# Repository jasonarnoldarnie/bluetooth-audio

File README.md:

# bluetooth-audio
Hardware and firmware for bluetooth audio adaptor

## Repo setup

Hooks live in `.githooks/` (version controlled), so each clone needs one command to enable them:

```bash
git config core.hooksPath .githooks
```

The `pre-commit` hook re-stamps the "Updated" date in [`docs/design-overview.tex`](docs/design-overview.tex)
and renders [`docs/design-overview.pdf`](docs/design-overview.pdf) into the same commit. It runs only
when that document is staged, never blocks a commit, and needs [Tectonic](https://tectonic-typesetting.github.io/)
(XeTeX) on `PATH` or in `%LOCALAPPDATA%\Programs\Tectonic` (Python is used only for the date stamp).
The diagrams render in the Consolas monospace font (a Windows system font); on other platforms swap it
for another mono font with box-drawing glyphs in the document preamble.

- `git config hooks.designpdf false` — disable without deleting the hook
- `git config hooks.designpdf.snapshot true` — also keep a dated copy under `docs/snapshots/`

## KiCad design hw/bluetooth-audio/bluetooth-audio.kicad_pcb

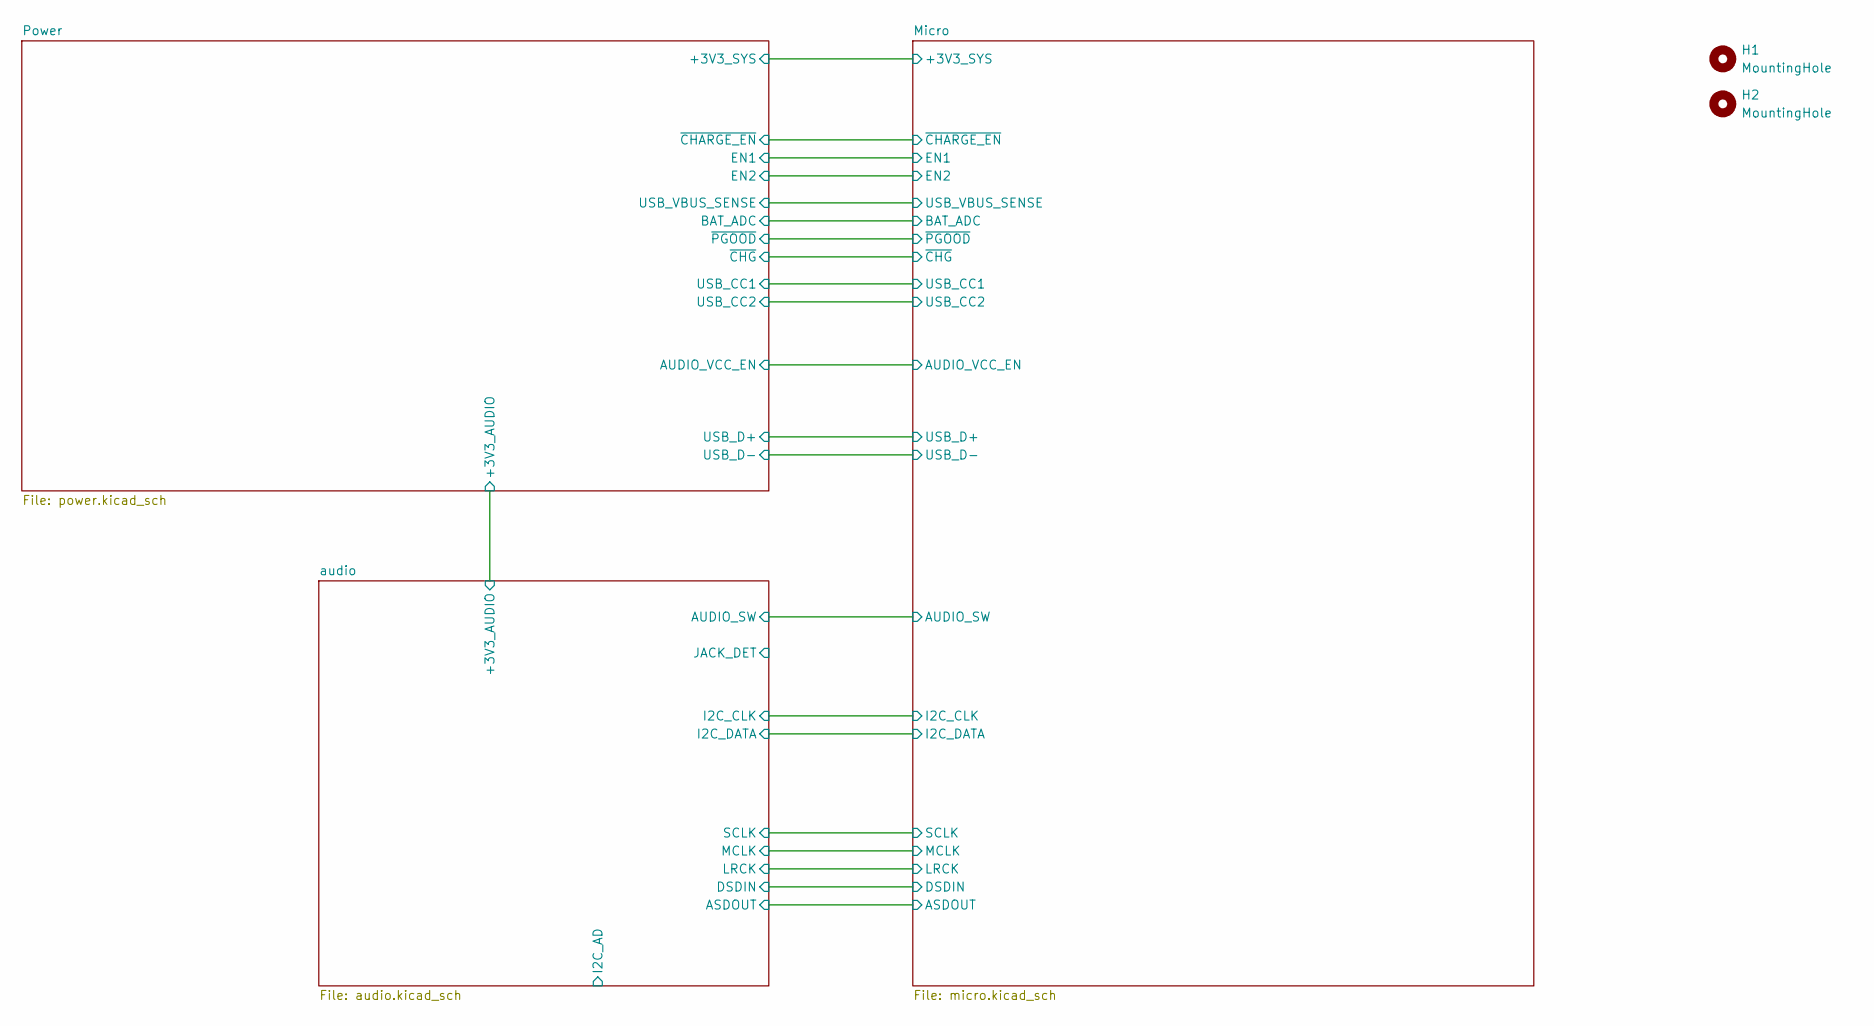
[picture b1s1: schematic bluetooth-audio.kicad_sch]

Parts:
H1, H2: MountingHole; MountingHole_2.2mm_M2_DIN965_Pad

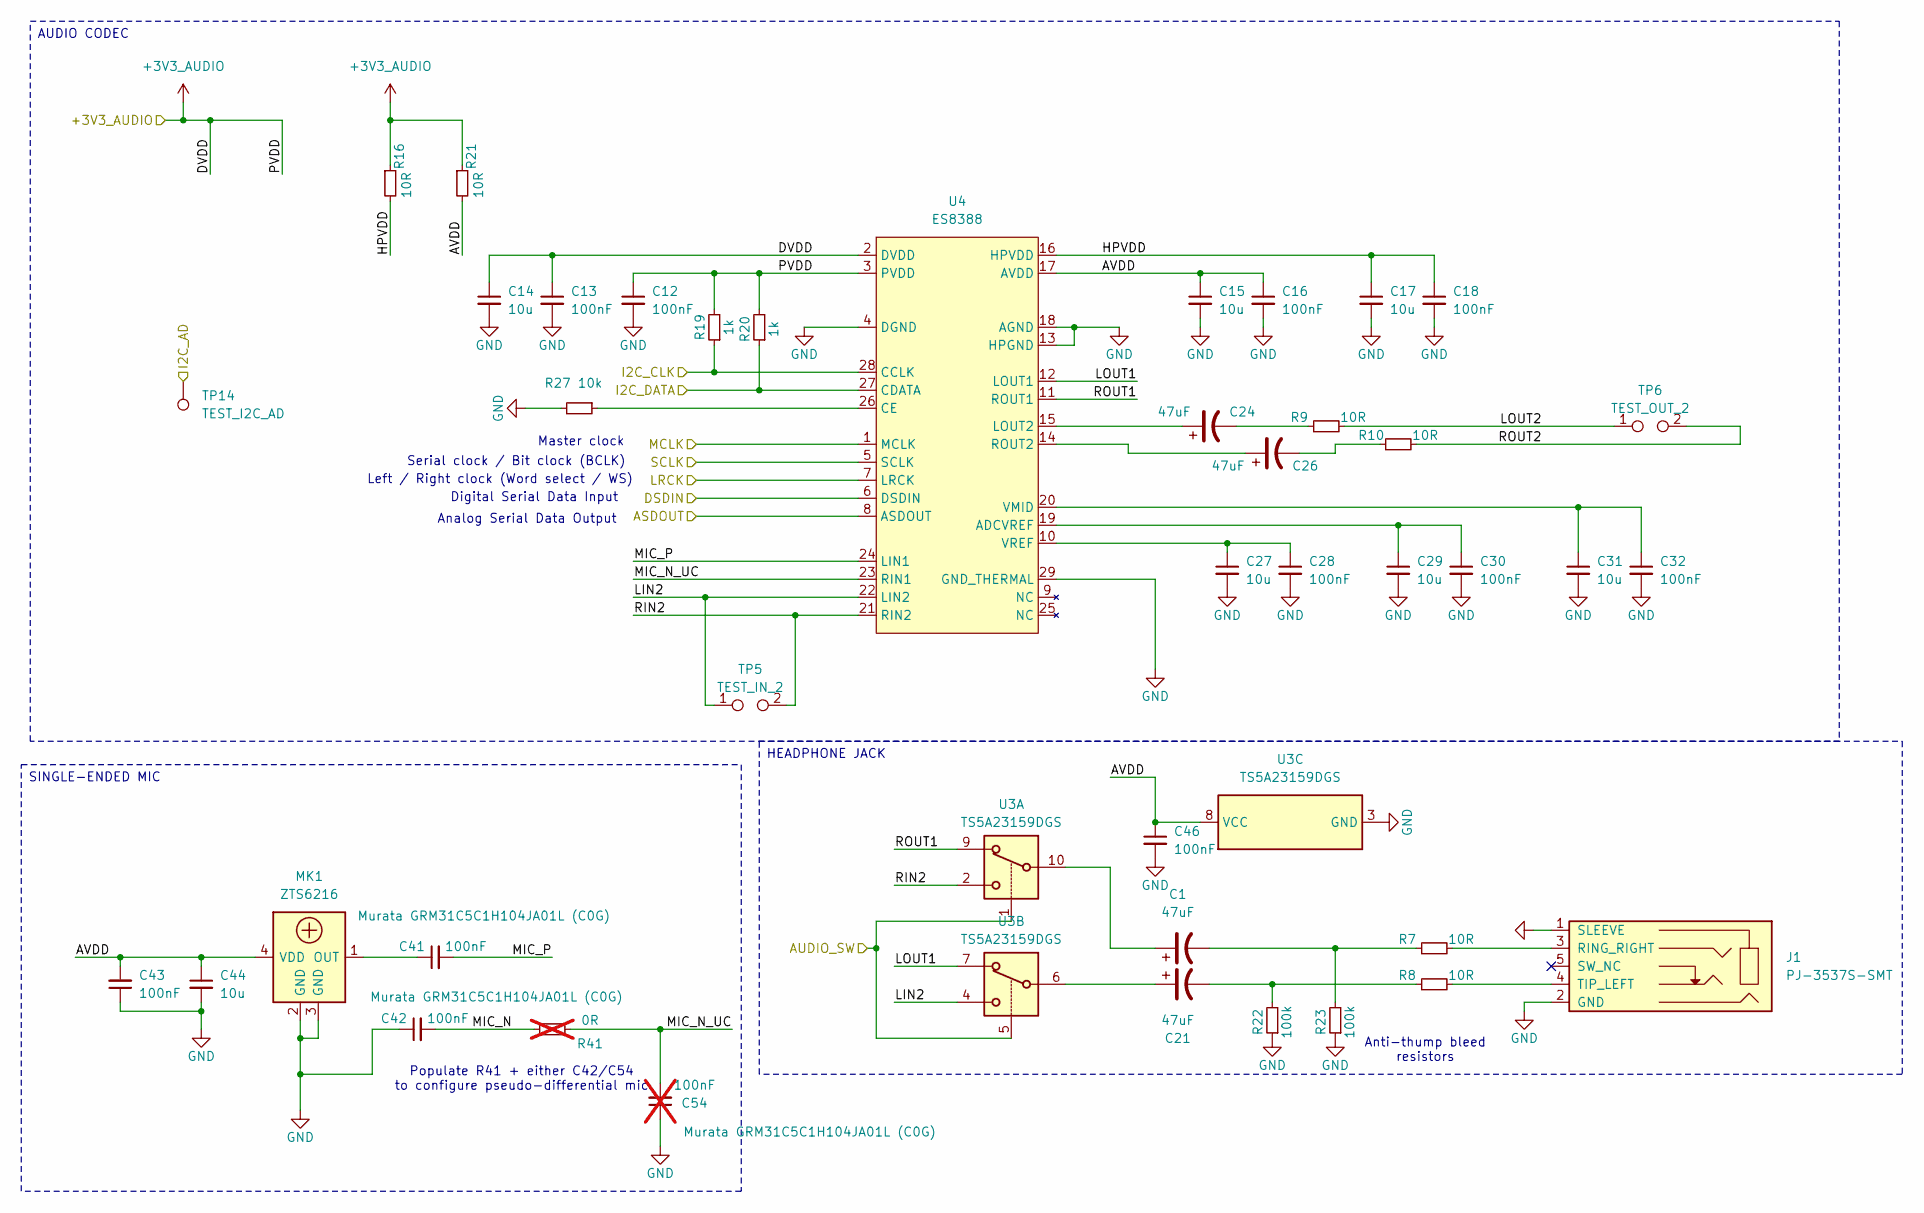
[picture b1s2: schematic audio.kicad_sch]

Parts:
C1, C21, C24, C26: 47uF; CP_Elec_5x5.8; MPN EEEFT1E470AR; LCSC C336270
C12, C13, C16, C18, C28, C30, C32, C43, C46: 100nF; C_0402_1005Metric; MPN CL05B104KO5NNNC; LCSC C1525
C14, C15, C17, C27, C29, C31, C44: 10u; C_0603_1608Metric; MPN CL10A106KP8NNNC; LCSC C19702
C41, C42: 100nF; C_1206_3216Metric; MPN GRM31C5C1H104JA01L; LCSC C97946
C54: 100nF; C_1206_3216Metric; MPN GRM31C5C1H104JA01L; LCSC C97946; not fitted
J1: PJ-3537S-SMT; MPN PJ-3537S-SMT; LCSC C2689709
MK1: ZTS6216; MPN ZTS6216; LCSC C481302
R7, R8, R9, R10, R16, R21: 10R; R_0402_1005Metric; MPN 0402WGF100JTCE; LCSC C25077
R19, R20: 1k; R_0402_1005Metric; MPN 0402WGF1001TCE; LCSC C11702
R22, R23: 100k; R_0402_1005Metric; MPN 0402WGF1003TCE; LCSC C25741
R27: 10k; R_0402_1005Metric; MPN 0402WGF1002TCE; LCSC C25744
R41: 0R; R_0402_1005Metric; MPN 0402WGF0000TCE; LCSC C17168; not fitted
TP5: TEST_IN_2; TestPoint_Pad_2x1_D1.0mm
TP6: TEST_OUT_2; TestPoint_Pad_2x1_D1.0mm
TP14: TEST_I2C_AD; TestPoint_Pad_D1.0mm
U3: TS5A23159DGS; MSOP-10_3x3mm_P0.5mm; MPN TS5A23159DGSR; LCSC C42751
U4: ES8388; QFN-28-1EP_4x4mm_P0.4mm_EP2.3x2.3mm; MPN ES8388; LCSC C365736

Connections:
+3V3_AUDIO: C12.1, C13.1, C14.1, R16.1, R19.2, R20.2, R21.1, U4.2 (DVDD), U4.3 (PVDD); also elsewhere on the board
/Micro/ASDOUT: U4.8 (ASDOUT); also elsewhere on the board
/Micro/AUDIO_SW: U3.1, U3.5; also elsewhere on the board
/Micro/DSDIN: U4.6 (DSDIN); also elsewhere on the board
/Micro/GPIO_0: U4.1 (MCLK); also elsewhere on the board
/Micro/I2C_CLK: R19.1, U4.28 (CCLK); also elsewhere on the board
/Micro/I2C_DATA: R20.1, U4.27 (CDATA); also elsewhere on the board
/Micro/LRCK: U4.7 (LRCK); also elsewhere on the board
/Micro/SCLK: U4.5 (SCLK); also elsewhere on the board
/audio/AVDD: C15.1, C16.1, C43.2, C44.1, C46.1, MK1.4 (VDD), R21.2, U3.8 (VCC), U4.17 (AVDD)
/audio/HPVDD: C17.1, C18.1, R16.2, U4.16 (HPVDD)
/audio/LIN2: TP5.1, U3.4, U4.22 (LIN2)
/audio/LOUT1: U3.7, U4.12 (LOUT1)
/audio/LOUT2: R9.2, TP6.1
/audio/MIC_N: C42.2, R41.1
/audio/MIC_N_UC: C54.2, R41.2, U4.23 (RIN1)
/audio/MIC_P: C41.2, U4.24 (LIN1)
/audio/RIN2: TP5.2, U3.2, U4.21 (RIN2)
/audio/ROUT1: U3.9, U4.11 (ROUT1)
/audio/ROUT2: R10.2, TP6.2
GND: C12.2, C13.2, C14.2, C15.2, C16.2, C17.2, C18.2, C27.2, C28.2, C29.2, C30.2, C31.2, C32.2, C42.1, C43.1, C44.2, C46.2, C54.1, J1.1 (SLEEVE), J1.2 (GND), MK1.2 (GND), MK1.3 (GND), R22.1, R23.1, R27.2, U3.3 (GND), U4.4 (DGND), U4.13 (HPGND), U4.18 (AGND), U4.29 (GND_THERMAL); also elsewhere on the board
unnamed: C1.1, U3.10
unnamed: C1.2, R7.1, R23.2
unnamed: C21.1, U3.6
unnamed: C21.2, R8.1, R22.2
unnamed: C24.2, R9.1
unnamed: C26.2, R10.1
unnamed: J1.3 (RING_RIGHT), R7.2
unnamed: J1.4 (TIP_LEFT), R8.2
unnamed: C41.1, MK1.1 (OUT)
unnamed: C29.1, C30.1, U4.19 (ADCVREF)
unnamed: R27.1, U4.26 (CE)
unnamed: C24.1, U4.15 (LOUT2)
unnamed: C26.1, U4.14 (ROUT2)
unnamed: C31.1, C32.1, U4.20 (VMID)
unnamed: C27.1, C28.1, U4.10 (VREF)

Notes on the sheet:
Anti-thump bleed resistors
Digital Serial Data Input
Left / Right clock (Word select / WS)
Populate R41 + either C42/C54 to configure pseudo-differential mic
Analog Serial Data Output
Master clock
Serial clock / Bit clock (BCLK)
SINGLE-ENDED MIC
HEADPHONE JACK
AUDIO CODEC

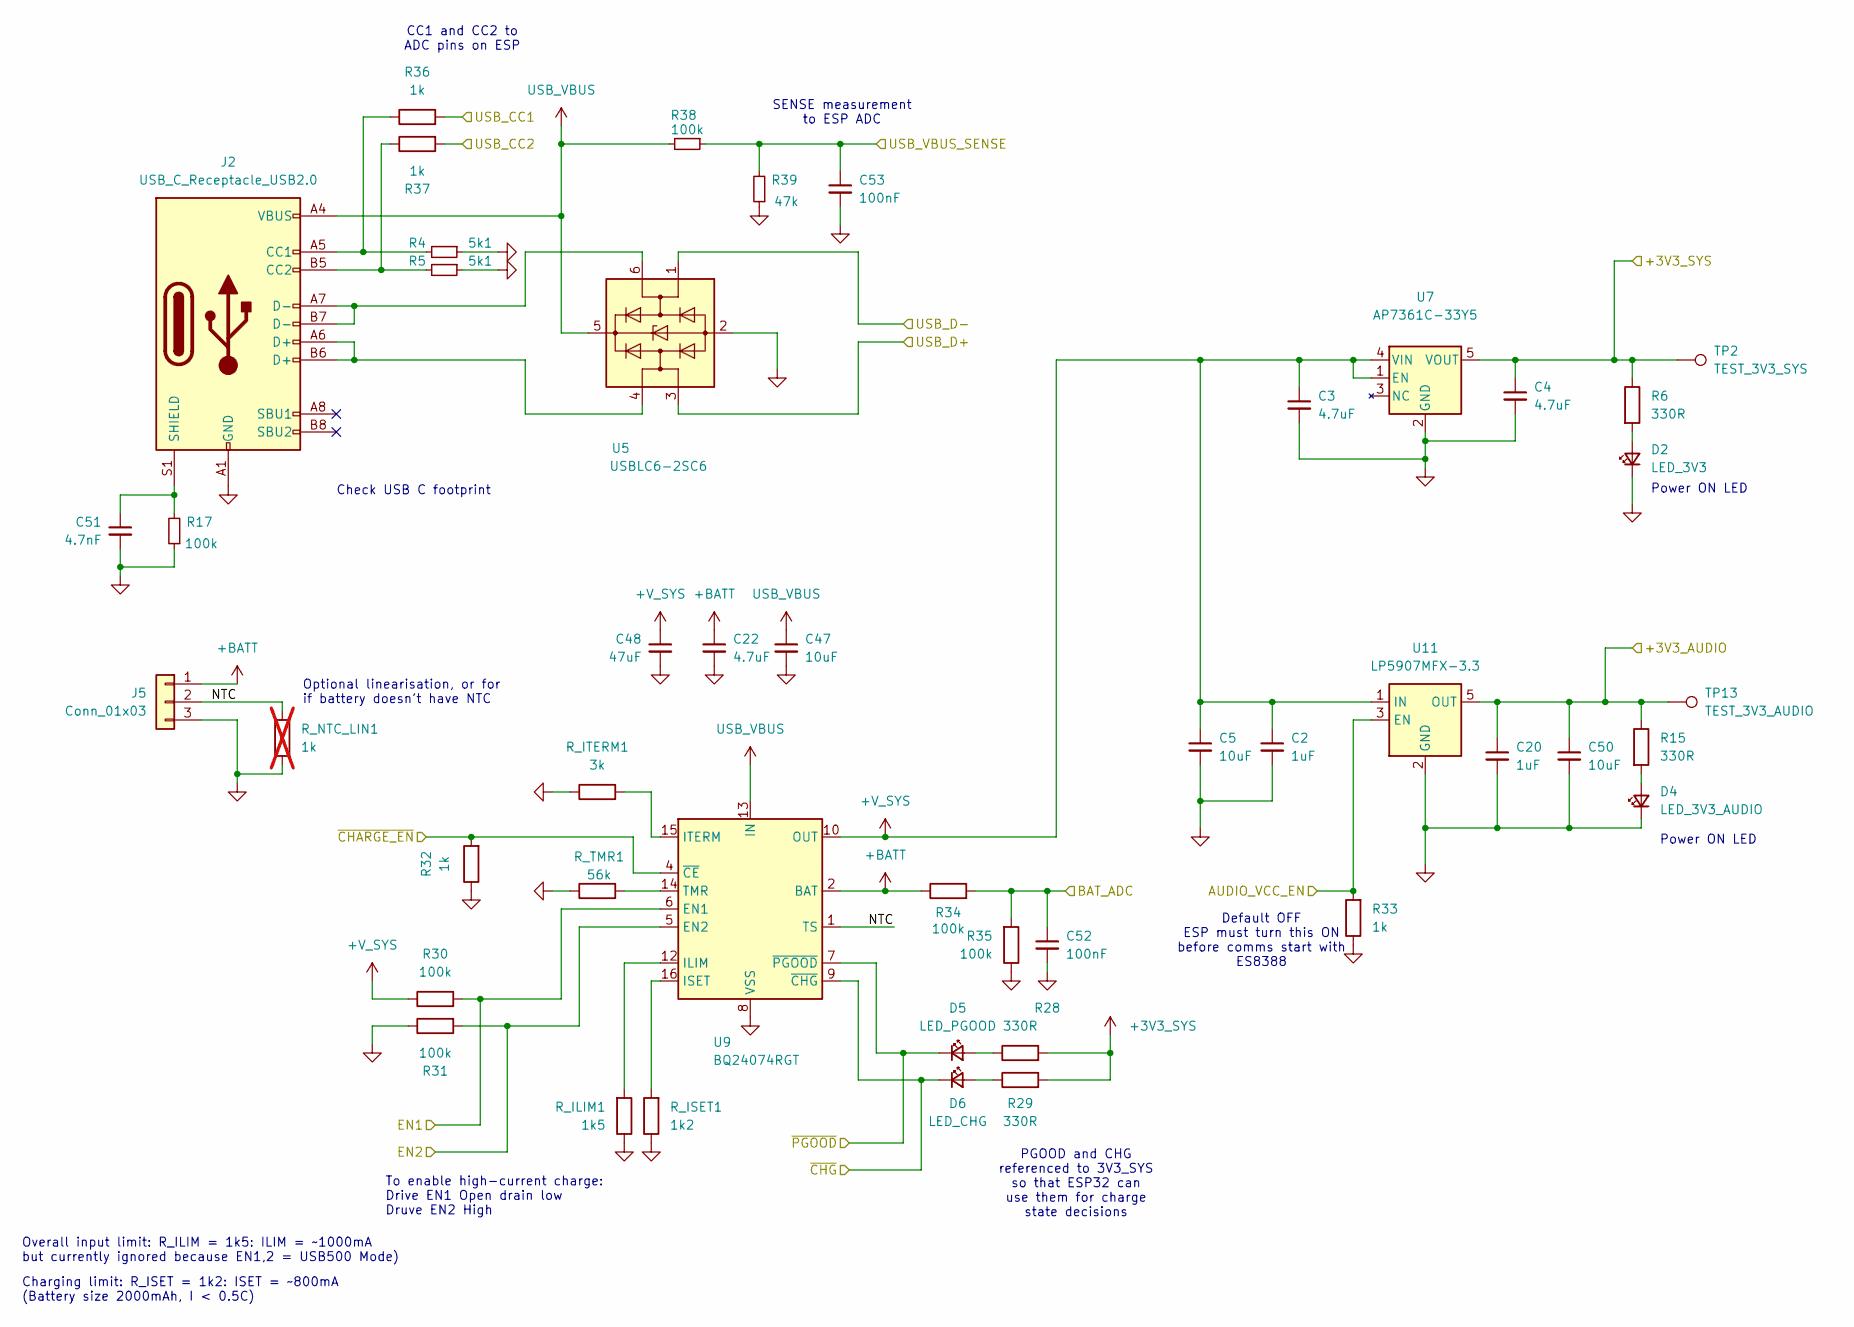
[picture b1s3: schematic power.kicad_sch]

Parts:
C2: 1uF; C_1206_3216Metric; MPN CL31B105KBHNNNE; LCSC C1848
C3: 4.7uF; C_1206_3216Metric; MPN 1206B475K500NT; LCSC C29823
C4, C22: 4.7uF; C_0603_1608Metric; MPN CL10A475KO8NNNC; LCSC C19666
C5, C47, C50: 10uF; C_1206_3216Metric; MPN CL31A106KBHNNNE; LCSC C13585
C20: 1uF; C_0603_1608Metric; MPN CL10A105KB8NNNC; LCSC C15849
C48: 47uF; CP_EIA-3528-21_Kemet-B; MPN TAJB476K010RNJ; LCSC C22036
C51: 4.7nF; C_0402_1005Metric; MPN 0402B472K500NT; LCSC C1538
C52: 100nF; C_1206_3216Metric; MPN CL31B104KBCNNNC; LCSC C24497
C53: 100nF; C_0402_1005Metric; MPN CL05B104KO5NNNC; LCSC C1525
D2: LED_3V3; LED_0805_2012Metric; MPN KT-0805G; LCSC C2297
D4: LED_3V3_AUDIO; LED_0805_2012Metric; MPN KT-0805G; LCSC C2297
D5: LED_PGOOD; LED_0805_2012Metric; MPN KT-0805G; LCSC C2297
D6: LED_CHG; LED_0805_2012Metric; MPN KT-0805Y; LCSC C2296
J2: USB_C_Receptacle_USB2.0; USB_C_Receptacle_GCT_USB4110; MPN USB4110-GF-A; LCSC C5143397
J5: Conn_01x03; JST_PH_S3B-PH-K_1x03_P2.00mm_Horizontal; MPN S3B-PH-K-S(LF)(SN); LCSC C157929
R4, R5: 5k1; R_0402_1005Metric; MPN 0402WGF5101TCE; LCSC C25905
R6, R15, R28, R29: 330R; R_0402_1005Metric; MPN 0402WGF3300TCE; LCSC C25104
R17, R30, R31, R34, R35, R38: 100k; R_0402_1005Metric; MPN 0402WGF1003TCE; LCSC C25741
R32, R33, R36, R37: 1k; R_0402_1005Metric; MPN 0402WGF1001TCE; LCSC C11702
R39: 47k; R_0402_1005Metric; MPN 0402WGF4702TCE; LCSC C25792
R_ILIM1: 1k5; R_0402_1005Metric; MPN 0402WGF1501TCE; LCSC C25867
R_ISET1: 1k2; R_0402_1005Metric; MPN 0402WGF1201TCE; LCSC C25862
R_ITERM1: 3k; R_0402_1005Metric; MPN 0402WGF3001TCE; LCSC C25784
R_NTC_LIN1: 1k; R_0402_1005Metric; MPN 0402WGF1001TCE; LCSC C11702; not fitted
R_TMR1: 56k; R_0402_1005Metric; MPN 0402WGF5602TCE; LCSC C25796
TP2: TEST_3V3_SYS; TestPoint_Pad_D1.0mm
TP13: TEST_3V3_AUDIO; TestPoint_Pad_D1.0mm
U5: USBLC6-2SC6; SOT-23-6; MPN USBLC6-2SC6; LCSC C7519
U7: AP7361C-33Y5; SOT-89-5; MPN AP7361C-33Y5-13; LCSC C460397
U9: BQ24074RGT; VQFN-16-1EP_3x3mm_P0.5mm_EP1.6x1.6mm; MPN BQ24074RGTR; LCSC C54313
U11: LP5907MFX-3.3; SOT-23-5; MPN LP5907MFX-3.3/NOPB; LCSC C80670

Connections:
+3V3_AUDIO: C20.1, C50.1, R15.1, TP13.1 (1_1), U11.5 (OUT); also elsewhere on the board
+3V3_SYS: C4.1, R6.1, R28.2, R29.2, TP2.1 (1_1), U7.5 (VOUT); also elsewhere on the board
+BATT: C22.1, J5.1, R34.1, U9.2 (BAT), U9.3 (BAT)
+V_SYS: C2.1, C3.1, C5.1, C48.1, R30.1, U7.1 (EN), U7.4 (VIN), U9.10 (OUT), U9.11 (OUT), U11.1 (IN)
/Micro/AUDIO_VCC_EN: R33.2, U11.3 (EN); also elsewhere on the board
/Micro/BAT_ADC: C52.1, R34.2, R35.2; also elsewhere on the board
/Micro/EN1: R30.2, U9.6 (EN1); also elsewhere on the board
/Micro/EN2: R31.2, U9.5 (EN2); also elsewhere on the board
/Micro/USB_CC1: R36.2; also elsewhere on the board
/Micro/USB_CC2: R37.2; also elsewhere on the board
/Micro/USB_D+: U5.3 (I/O2); also elsewhere on the board
/Micro/USB_D-: U5.1 (I/O1); also elsewhere on the board
/Micro/USB_VBUS_SENSE: C53.1, R38.1, R39.2; also elsewhere on the board
/Micro/~CHARGE_EN: R32.2, U9.4 (~CE); also elsewhere on the board
/Micro/~CHG: D6.1 (K), U9.9 (~CHG); also elsewhere on the board
/Micro/~PGOOD: D5.1 (K), U9.7 (~PGOOD); also elsewhere on the board
/Power/NTC: J5.2, R_NTC_LIN1.2, U9.1 (TS)
/Power/USB_CONN_D+: J2.A6 (D+), J2.B6 (D+), U5.4 (I/O2)
/Power/USB_CONN_D-: J2.A7 (D-), J2.B7 (D-), U5.6 (I/O1)
GND: C2.2, C3.2, C4.2, C5.2, C20.2, C22.2, C47.2, C48.2, C50.2, C51.2, C52.2, C53.2, D2.1 (K), D4.1 (K), J2.A1 (GND), J2.A12 (GND), J2.B1 (GND), J2.B12 (GND), J5.3, R4.1, R5.1, R17.1, R31.1, R32.1, R33.1, R35.1, R39.1, R_ILIM1.1, R_ISET1.1, R_ITERM1.1, R_NTC_LIN1.1, R_TMR1.1, U5.2 (GND), U7.2 (GND), U9.8 (VSS), U9.17 (VSS), U11.2 (GND); also elsewhere on the board
unnamed: D2.2 (A), R6.2
unnamed: D4.2 (A), R15.2
unnamed: D5.2 (A), R28.1
unnamed: D6.2 (A), R29.1
unnamed: J2.A5 (CC1), R4.2, R36.1
unnamed: J2.B5 (CC2), R5.2, R37.1
unnamed: C51.1, J2.S1 (SHIELD), R17.2
unnamed: R_ILIM1.2, U9.12 (ILIM)
unnamed: R_ISET1.2, U9.16 (ISET)
unnamed: R_ITERM1.2, U9.15 (ITERM)
unnamed: R_TMR1.2, U9.14 (TMR)
USB_VBUS: C47.1, J2.A4 (VBUS), J2.A9 (VBUS), J2.B4 (VBUS), J2.B9 (VBUS), R38.2, U5.5 (VBUS), U9.13 (IN)

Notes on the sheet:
Charging limit: R_ISET = 1k2: ISET = ~800mA (Battery size 2000mAh, I < 0.5C)
Check USB C footprint
CC1 and CC2 to ADC pins on ESP
To enable high-current charge: Drive EN1 Open drain low Druve EN2 High
Power ON LED
Overall input limit: R_ILIM = 1k5: ILIM = ~1000mA but currently ignored because EN1,2 = USB500 Mode)
SENSE measurement to ESP ADC
PGOOD and CHG referenced to 3V3_SYS so that ESP32 can use them for charge state decisions
Default OFF ESP must turn this ON before comms start with ES8388
Optional linearisation, or for if battery doesn't have NTC

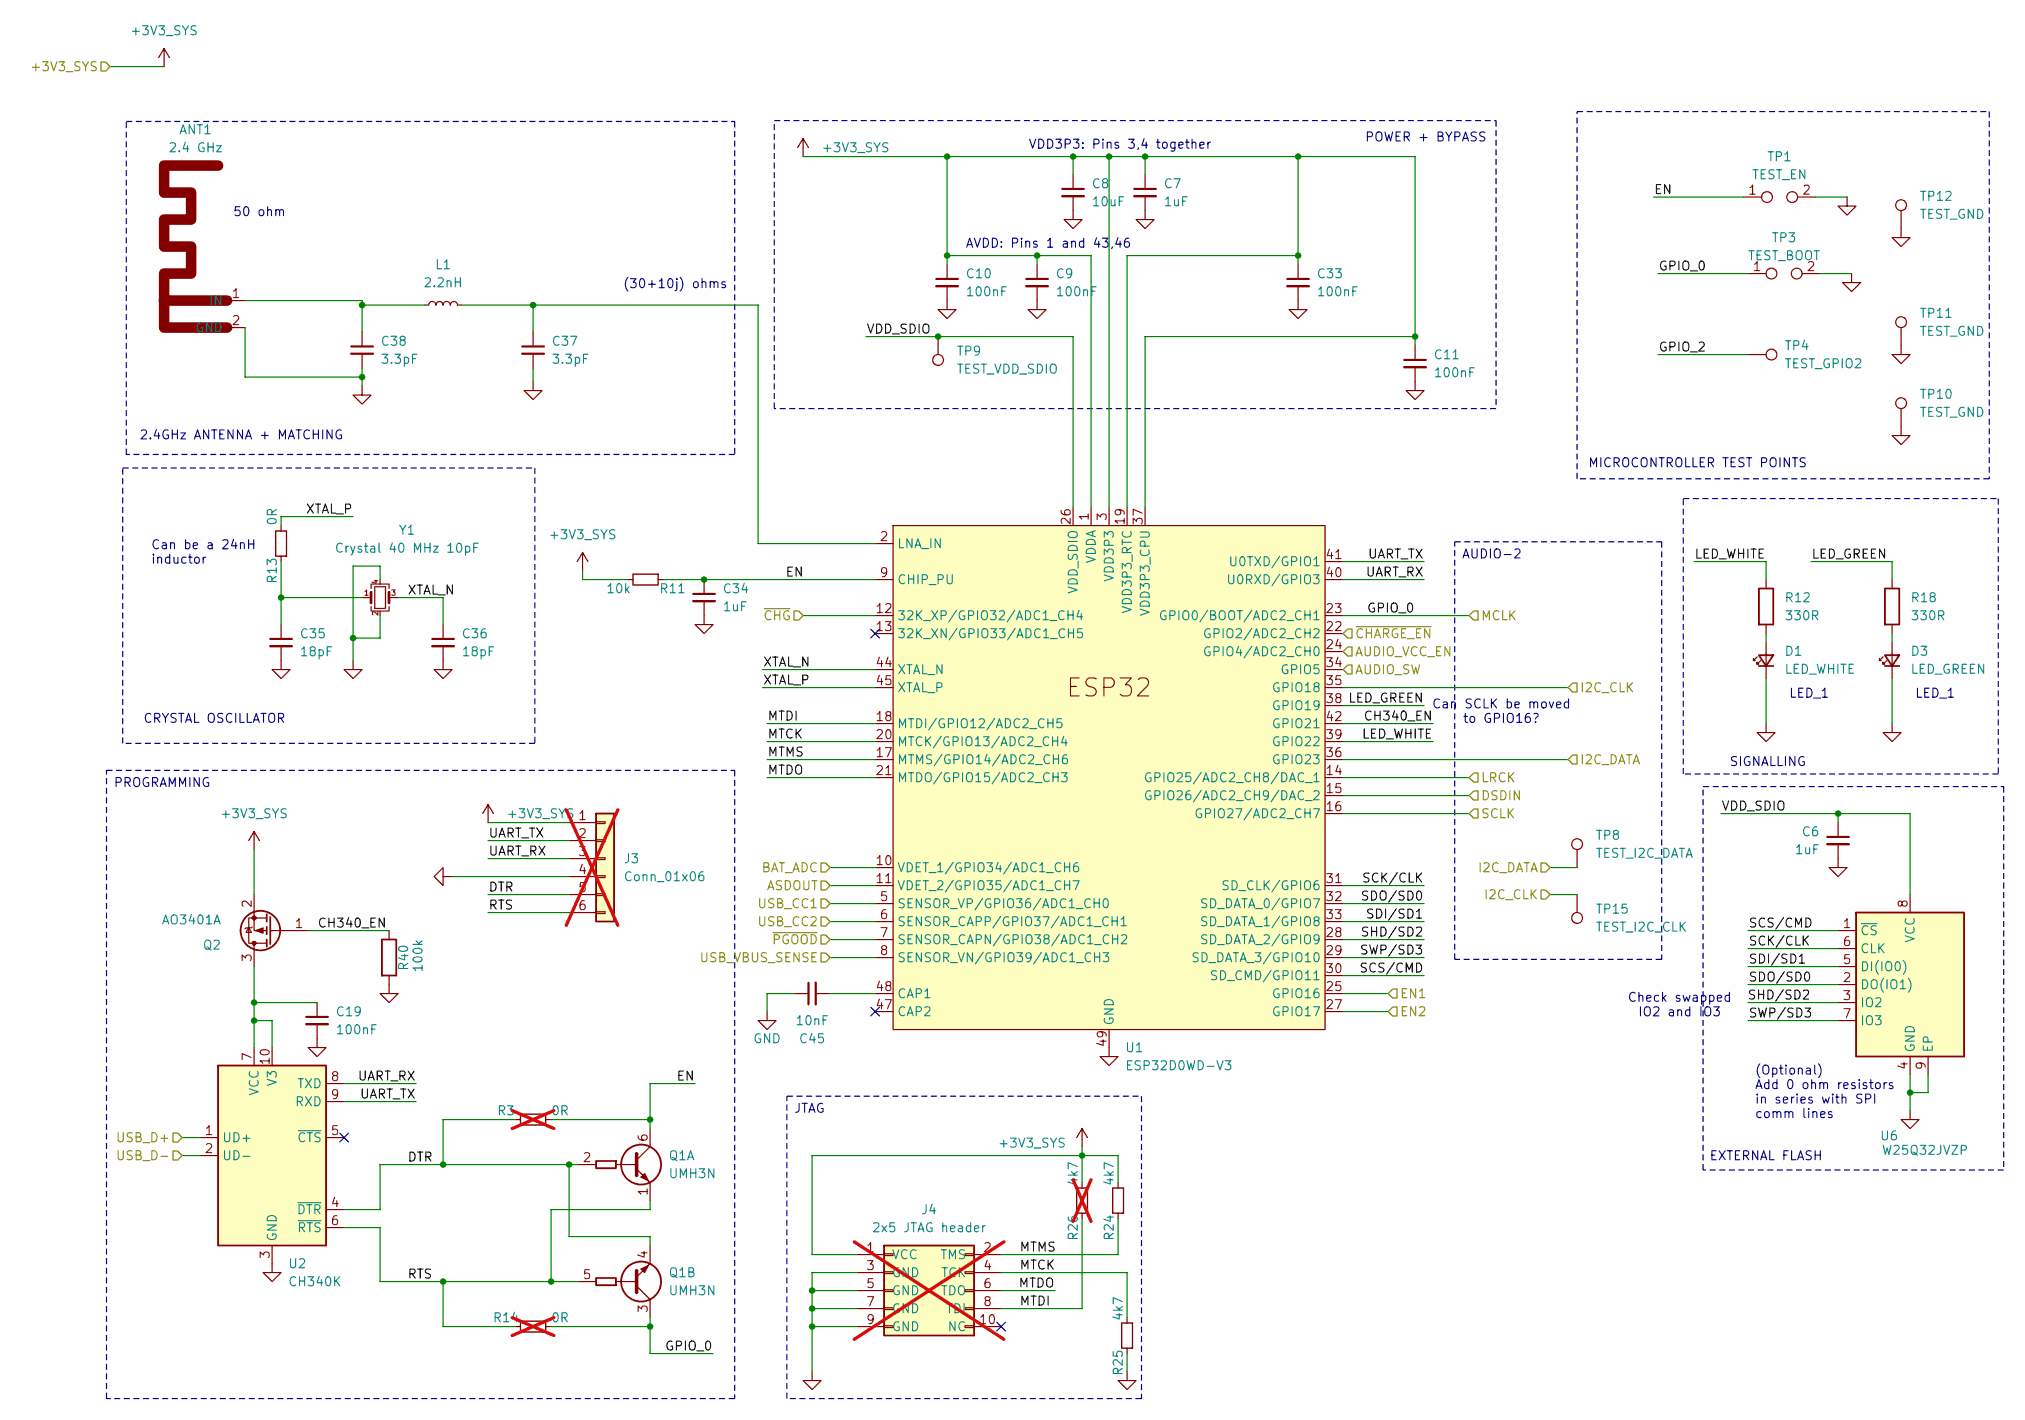
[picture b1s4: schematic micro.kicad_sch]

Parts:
ANT1: 2.4 GHz; Antenna 2.4GHz Inverted-F Meandered
C6, C7, C34: 1uF; C_0402_1005Metric; MPN CL05A105KA5NQNC; LCSC C52923
C8: 10uF; C_0603_1608Metric; MPN CL10A106KP8NNNC; LCSC C19702
C9, C10, C11, C19, C33: 100nF; C_0402_1005Metric; MPN CL05B104KO5NNNC; LCSC C1525
C35, C36: 18pF; C_0402_1005Metric; MPN 0402CG180J500NT; LCSC C1549
C37, C38: 3.3pF; C_0402_1005Metric; MPN GJM1555C1H3R3BB01D; LCSC C76906
C45: 10nF; C_0402_1005Metric; MPN CL05B103KB5NNNC; LCSC C15195
D1: LED_WHITE; LED_0805_2012Metric; MPN KT-0805W; LCSC C34499
D3: LED_GREEN; LED_0805_2012Metric; MPN KT-0805G; LCSC C2297
J3: Conn_01x06; PinHeader_1x06_P2.54mm_Vertical; not fitted
J4: 2x5 JTAG header; 2x5 2mm JTAG header pads only; not fitted
L1: 2.2nH; L_0402_1005Metric; MPN LQG15HS2N2S02D; LCSC C86061
Q1: UMH3N; SOT-363_SC-70-6; MPN UMH3N; LCSC C62892
Q2: AO3401A; SOT-23; MPN AO3401A; LCSC C15127
R3, R14: 0R; R_0402_1005Metric; MPN 0402WGF0000TCE; LCSC C17168; not fitted
R11: 10k; R_0402_1005Metric; MPN 0402WGF1002TCE; LCSC C25744
R12, R18: 330R; R_0402_1005Metric; MPN 0402WGF3300TCE; LCSC C25104
R13: 0R; R_0402_1005Metric; MPN 0402WGF0000TCE; LCSC C17168
R24, R25: 4k7; R_0402_1005Metric; MPN 0402WGF4701TCE; LCSC C25900
R26: 4k7; R_0402_1005Metric; MPN 0402WGF4701TCE; LCSC C25900; not fitted
R40: 100k; R_0402_1005Metric; MPN 0402WGF1003TCE; LCSC C25741
TP1: TEST_EN; TestPoint_Pad_2x1_D1.0mm
TP3: TEST_BOOT; TestPoint_Pad_2x1_D1.0mm
TP4: TEST_GPIO2; TestPoint_Pad_D1.0mm
TP8: TEST_I2C_DATA; TestPoint_Pad_D1.0mm
TP9: TEST_VDD_SDIO; TestPoint_Pad_D1.0mm
TP10, TP11, TP12: TEST_GND; TestPoint_Pad_D1.0mm
TP15: TEST_I2C_CLK; TestPoint_Pad_D1.0mm
U1: ESP32D0WD-V3; QFN-48-1EP_5x5mm_P0.35mm_EP3.7x3.7mm_ThermalVias; MPN ESP32-D0WD-V3; LCSC C967021
U2: CH340K; SSOP-10-1EP_3.9x4.9mm_P1mm_EP2.1x3.3mm; MPN CH340K; LCSC C968586
U6: W25Q32JVZP; WSON-8-1EP_6x5mm_P1.27mm_EP3.4x4.3mm; MPN W25Q32JVZPIQ; LCSC C571260
Y1: Crystal 40 MHz 10pF; Crystal_SMD_2520-4Pin_2.5x2.0mm; MPN E2SB40E000006E; LCSC C1021653

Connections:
+3V3_SYS: C7.1, C8.1, C9.1, C10.1, C11.1, C33.1, J3.1, J4.1 (VCC), Q2.2 (S), R11.2, R24.2, R26.2, U1.1 (VDDA), U1.3 (VDD3P3), U1.4 (VDD3P3), U1.19 (VDD3P3_RTC), U1.37 (VDD3P3_CPU), U1.43 (VDDA), U1.46 (VDDA); also elsewhere on the board
/Micro/ANT_FEED: ANT1.1 (IN), C38.1, L1.1
/Micro/ASDOUT: U1.11 (VDET_2/GPIO35/ADC1_CH7); also elsewhere on the board
/Micro/AUDIO_SW: U1.34 (GPIO5); also elsewhere on the board
/Micro/AUDIO_VCC_EN: U1.22 (GPIO2/ADC2_CH2); also elsewhere on the board
/Micro/BAT_ADC: U1.8 (SENSOR_VN/GPIO39/ADC1_CH3); also elsewhere on the board
/Micro/CH340_EN: Q2.1 (G), R40.1, U1.42 (GPIO21)
/Micro/DSDIN: U1.15 (GPIO26/ADC2_CH9/DAC_2); also elsewhere on the board
/Micro/DTR: J3.5, Q1.2 (B1), Q1.4 (E2), R3.1, U2.4 (~DTR)
/Micro/EN: C34.1, Q1.6 (C1), R3.2, R11.1, TP1.1, U1.9 (CHIP_PU)
/Micro/EN1: U1.27 (GPIO17); also elsewhere on the board
/Micro/EN2: U1.25 (GPIO16); also elsewhere on the board
/Micro/GPIO_0: Q1.3 (C2), R14.2, TP3.1, U1.23 (GPIO0/BOOT/ADC2_CH1); also elsewhere on the board
/Micro/GPIO_2: TP4.1 (1_1)
/Micro/I2C_CLK: TP15.1 (1_1), U1.35 (GPIO18); also elsewhere on the board
/Micro/I2C_DATA: TP8.1 (1_1), U1.36 (GPIO23); also elsewhere on the board
/Micro/LED_GREEN: R18.1, U1.38 (GPIO19)
/Micro/LED_WHITE: R12.1, U1.39 (GPIO22)
/Micro/LNA_IN: C37.1, L1.2, U1.2 (LNA_IN)
/Micro/LRCK: U1.14 (GPIO25/ADC2_CH8/DAC_1); also elsewhere on the board
/Micro/MTCK: J4.4 (TCK), R25.2, U1.20 (MTCK/GPIO13/ADC2_CH4)
/Micro/MTDI: J4.8 (TDI), R26.1, U1.18 (MTDI/GPIO12/ADC2_CH5)
/Micro/MTDO: J4.6 (TDO), U1.21 (MTDO/GPIO15/ADC2_CH3)
/Micro/MTMS: J4.2 (TMS), R24.1, U1.17 (MTMS/GPIO14/ADC2_CH6)
/Micro/RTS: J3.6, Q1.1 (E1), Q1.5 (B2), R14.1, U2.6 (~RTS)
/Micro/SCK/CLK: U1.31 (SD_CLK/GPIO6), U6.6 (CLK)
/Micro/SCLK: U1.16 (GPIO27/ADC2_CH7); also elsewhere on the board
/Micro/SCS/CMD: U1.30 (SD_CMD/GPIO11), U6.1 (~CS)
/Micro/SDI/SD1: U1.33 (SD_DATA_1/GPIO8), U6.5 (DI(IO0))
/Micro/SDO/SD0: U1.32 (SD_DATA_0/GPIO7), U6.2 (DO(IO1))
/Micro/SHD/SD2: U1.28 (SD_DATA_2/GPIO9), U6.3 (IO2)
/Micro/SWP/SD3: U1.29 (SD_DATA_3/GPIO10), U6.7 (IO3)
/Micro/UART_RX: J3.3, U1.40 (U0RXD/GPIO3), U2.8 (TXD)
/Micro/UART_TX: J3.2, U1.41 (U0TXD/GPIO1), U2.9 (RXD)
/Micro/USB_CC1: U1.6 (SENSOR_CAPP/GPIO37/ADC1_CH1); also elsewhere on the board
/Micro/USB_CC2: U1.5 (SENSOR_VP/GPIO36/ADC1_CH0); also elsewhere on the board
/Micro/USB_D+: U2.1 (UD+); also elsewhere on the board
/Micro/USB_D-: U2.2 (UD-); also elsewhere on the board
/Micro/USB_VBUS_SENSE: U1.10 (VDET_1/GPIO34/ADC1_CH6); also elsewhere on the board
/Micro/VDD_SDIO: C6.1, TP9.1 (1_1), U1.26 (VDD_SDIO), U6.8 (VCC)
/Micro/XTAL_N: C36.1, U1.44 (XTAL_N), Y1.3
/Micro/XTAL_P: R13.2, U1.45 (XTAL_P)
/Micro/~CHARGE_EN: U1.24 (GPIO4/ADC2_CH0); also elsewhere on the board
/Micro/~CHG: U1.12 (32K_XP/GPIO32/ADC1_CH4); also elsewhere on the board
/Micro/~PGOOD: U1.7 (SENSOR_CAPN/GPIO38/ADC1_CH2); also elsewhere on the board
GND: ANT1.2 (GND), C6.2, C7.2, C8.2, C9.2, C10.2, C11.2, C19.2, C33.2, C34.2, C35.2, C36.2, C37.2, C38.2, C45.1, D1.1 (K), D3.1 (K), J3.4, J4.3 (GND), J4.5 (GND), J4.7 (GND), J4.9 (GND), R25.1, R40.2, TP1.2, TP3.2, TP10.1 (1_1), TP11.1 (1_1), TP12.1 (1_1), U1.49 (GND), U2.3 (GND), U2.11 (GND), U6.4 (GND), U6.9 (EP), Y1.2, Y1.4; also elsewhere on the board
unnamed: C35.1, R13.1, Y1.1
unnamed: D1.2 (A), R12.2
unnamed: D3.2 (A), R18.2
unnamed: C19.1, Q2.3 (D), U2.7 (VCC), U2.10 (V3)
unnamed: C45.2, U1.48 (CAP1)

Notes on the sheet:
MICROCONTROLLER TEST POINTS
LED_1
(30+10j) ohms
50 ohm
SIGNALLING
2.4GHz ANTENNA + MATCHING
(Optional) Add 0 ohm resistors in series with SPI comm lines
VDD3P3: Pins 3,4 together
EXTERNAL FLASH
AVDD: Pins 1 and 43,46
Check swapped IO2 and IO3
POWER + BYPASS
CRYSTAL OSCILLATOR
Can be a 24nH inductor
Can SCLK be moved to GPIO16?
AUDIO-2
JTAG
PROGRAMMING
